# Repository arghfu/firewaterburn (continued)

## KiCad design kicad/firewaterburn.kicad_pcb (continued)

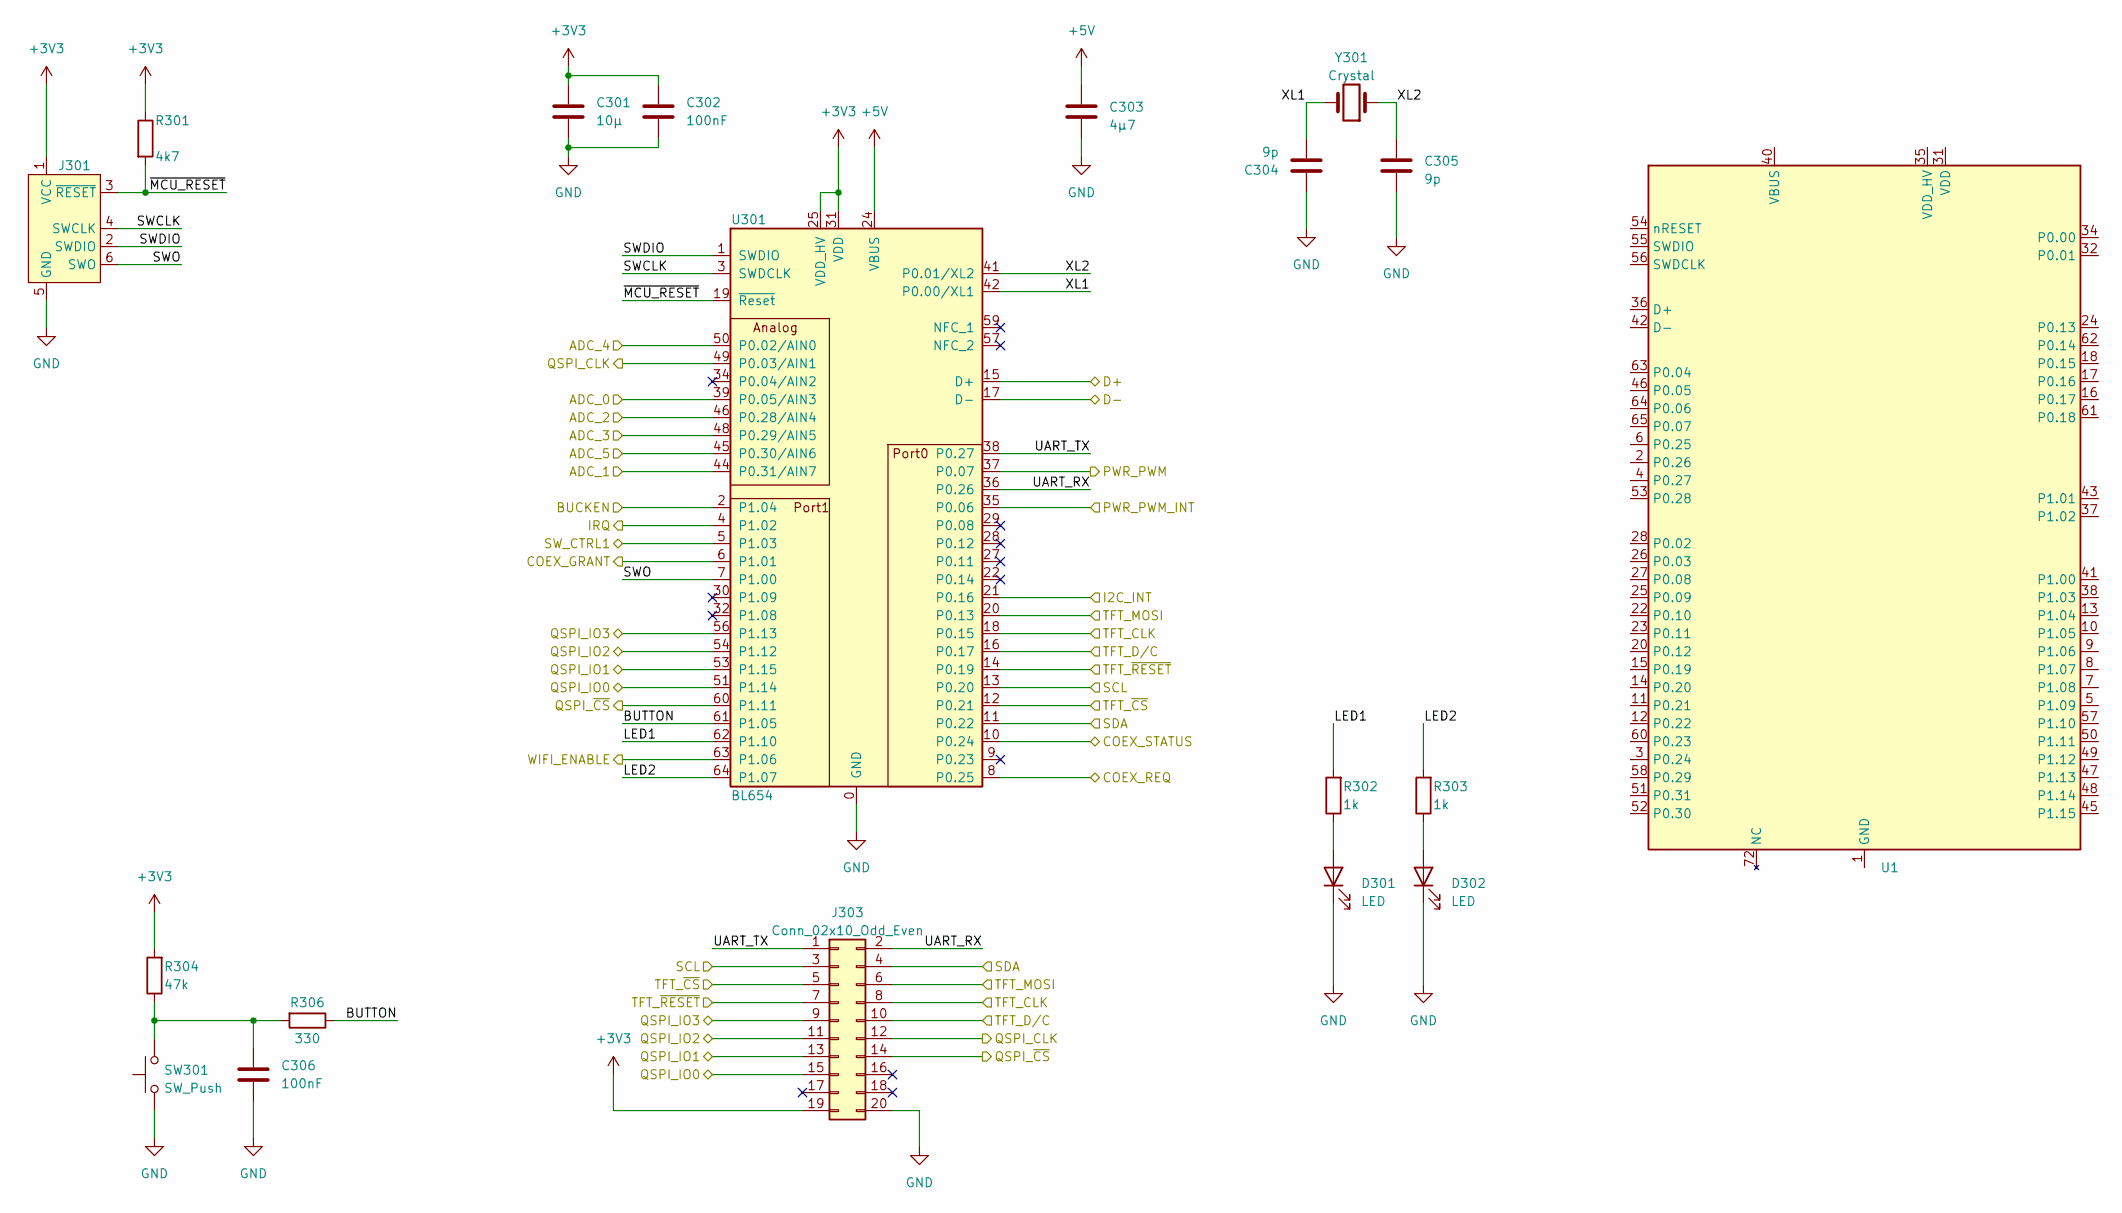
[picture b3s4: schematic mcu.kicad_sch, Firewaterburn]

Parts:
C301: 10µ; C_0603_1608Metric; Digikey 490-18214-1-ND
C302, C306: 100nF; C_0603_1608Metric; Digikey 1276-1006-1-ND
C303: 4µ7; C_0603_1608Metric; Digikey 478-06033D475KAT2ACT-ND
C304, C305: 9p; C_0603_1608Metric; Digikey 445-5627-1-ND
D301, D302: LED; LED_0603_1608Metric; Digikey 516-HSMS-C197CT-ND
J301: Conn_ARM_SWD_TagConnect_TC2030; Tag-Connect_TC2030-IDC-FP_2x03_P1.27mm_Vertical
J303: Conn_02x10_Odd_Even; PinHeader_2x10_P1.27mm_Vertical_SMD; Digikey 1175-1637-ND
R301: 4k7; R_0603_1608Metric; Digikey 311-4.70KHRCT-ND
R302, R303: 1k; R_0603_1608Metric; Digikey RNCP0603FTD1K00CT-ND
R304: 47k; R_0603_1608Metric
R306: 330; R_0603_1608Metric
SW301: SW_Push; SW_Push_SPST_NO_Alps_SKRK
U1: BL5340
U301: BL654; BL654-00001; Digikey 451-00001CT-ND
Y301: Crystal; CM8V-T1A-2Pin_2.0x1.2mm; Digikey 2195-CM8V-T1A-32.768KHZ-9PF-20PPM-TA-QC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

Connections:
+3V3: C301.1, C302.1, J301.1 (VCC), J303.19, R301.1, R304.2, U301.25 (VDD_HV), U301.31 (VDD); also elsewhere on the board
+5V: C303.1, U301.24 (VBUS); also elsewhere on the board
/D+: U301.15 (D+); also elsewhere on the board
/D-: U301.17 (D-); also elsewhere on the board
/analog/probe0: U301.39 (P0.05/AIN3); also elsewhere on the board
/analog/probe1: U301.44 (P0.31/AIN7); also elsewhere on the board
/analog/probe2: U301.46 (P0.28/AIN4); also elsewhere on the board
/analog/probe3: U301.48 (P0.29/AIN5); also elsewhere on the board
/analog/probe4: U301.50 (P0.02/AIN0); also elsewhere on the board
/analog/probe5: U301.45 (P0.30/AIN6); also elsewhere on the board
/fan_control/PWM: U301.37 (P0.07); also elsewhere on the board
/fan_control/TACHO: U301.35 (P0.06); also elsewhere on the board
/mcu/BUCKEN: U301.2 (P1.04); also elsewhere on the board
/mcu/BUTTON: R306.1, U301.61 (P1.05)
/mcu/COEX_GRANT: U301.6 (P1.01); also elsewhere on the board
/mcu/COEX_REQ: U301.8 (P0.25); also elsewhere on the board
/mcu/COEX_STATUS: U301.10 (P0.24); also elsewhere on the board
/mcu/I2C_INT: U301.21 (P0.16); also elsewhere on the board
/mcu/IRQ: U301.4 (P1.02); also elsewhere on the board
/mcu/LED1: R302.2, U301.62 (P1.10)
/mcu/LED2: R303.2, U301.64 (P1.07)
/mcu/QSPI_CLK: J303.12, U301.49 (P0.03/AIN1); also elsewhere on the board
/mcu/QSPI_IO0: J303.15, U301.51 (P1.14); also elsewhere on the board
/mcu/QSPI_IO1: J303.13, U301.53 (P1.15); also elsewhere on the board
/mcu/QSPI_IO2: J303.11, U301.54 (P1.12); also elsewhere on the board
/mcu/QSPI_IO3: J303.9, U301.56 (P1.13); also elsewhere on the board
/mcu/QSPI_~CS: J303.14, U301.60 (P1.11); also elsewhere on the board
/mcu/SCL: J303.3, U301.13 (P0.20); also elsewhere on the board
/mcu/SDA: J303.4, U301.11 (P0.22); also elsewhere on the board
/mcu/SWCLK: J301.4 (SWCLK), U301.3 (SWDCLK)
/mcu/SWDIO: J301.2 (SWDIO), U301.1 (SWDIO)
/mcu/SWO: J301.6 (SWO), U301.7 (P1.00)
/mcu/SW_CTRL1: U301.5 (P1.03); also elsewhere on the board
/mcu/TFT_CLK: J303.8, U301.18 (P0.15); also elsewhere on the board
/mcu/TFT_D/C: J303.10, U301.16 (P0.17); also elsewhere on the board
/mcu/TFT_MOSI: J303.6, U301.20 (P0.13); also elsewhere on the board
/mcu/TFT_~CS: J303.5, U301.12 (P0.21); also elsewhere on the board
/mcu/TFT_~RESET: J303.7, U301.14 (P0.19); also elsewhere on the board
/mcu/UART_RX: J303.2, U301.36 (P0.26)
/mcu/UART_TX: J303.1, U301.38 (P0.27)
/mcu/WIFI_ENABLE: U301.63 (P1.06); also elsewhere on the board
/mcu/XL1: C304.2, U301.42 (P0.00/XL1), Y301.2
/mcu/XL2: C305.1, U301.41 (P0.01/XL2), Y301.1
/mcu/~MCU_RESET: J301.3 (~RESET), R301.2, U301.19 (~Reset)
unnamed: C306.1, R304.1, R306.2, SW301.2
unnamed: D301.2 (A), R302.1
unnamed: D302.2 (A), R303.1

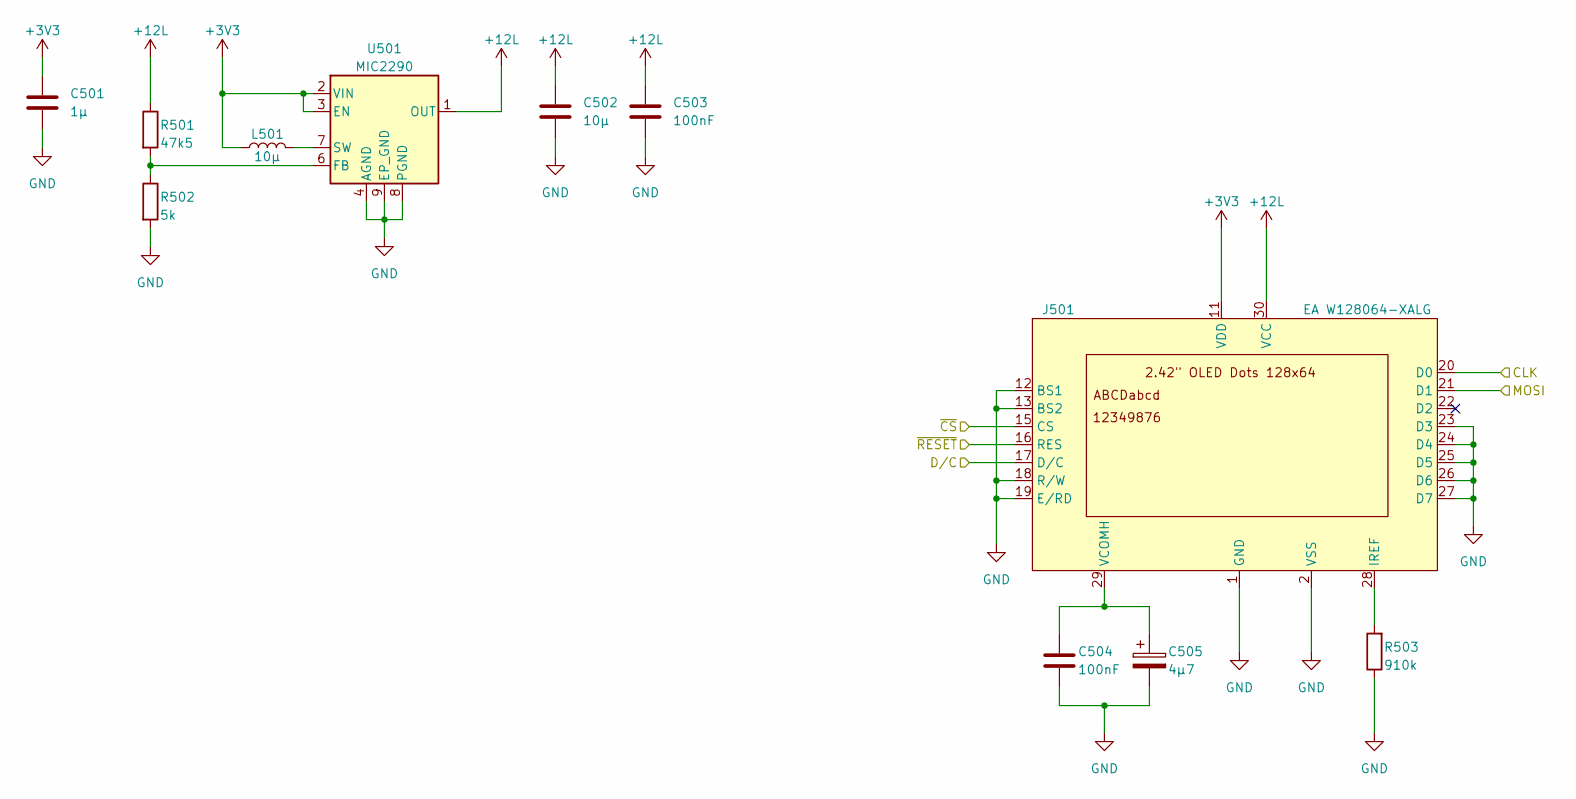
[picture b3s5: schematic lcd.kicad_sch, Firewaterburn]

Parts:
C501: 1µ; C_0402_1005Metric; Digikey 1276-1067-1-ND
C502: 10µ; C_0402_1005Metric; Digikey 490-GRM155R61A106ME11DCT-ND
C503: 100nF; C_0402_1005Metric; Digikey 478-7888-1-ND
C504: 100nF; C_0603_1608Metric; Digikey 1276-1006-1-ND
C505: 4µ7; CP_EIA-2012-15_AVX-P; Digikey 478-F981C475MMUAJ6CT-ND
J501: EA W128064-XALG; F32R-1A7H1-11031; Digikey EA W128064-XALG
L501: 10µ; L_Wuerth_MAPI-2510; Digikey 732-4851-1-ND
R501: 47k5; R_0402_1005Metric; Digikey 311-47.5KLRCT-ND
R502: 5k; R_0402_1005Metric; Digikey 13-RC0402FR-075KLCT-ND
R503: 910k; R_0603_1608Metric; Digikey 311-910KHRCT-ND
U501: MIC2290; Micrel_MLF-8-1EP_2x2mm_P0.5mm_EP0.8x1.3mm_ThermalVias; Digikey 576-1076-1-ND

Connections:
+3V3: C501.1, J501.11 (VDD), L501.1, U501.2 (VIN), U501.3 (EN); also elsewhere on the board
+12L: C502.1, C503.1, J501.30 (VCC), R501.1, U501.1 (OUT)
/mcu/TFT_CLK: J501.20 (D0); also elsewhere on the board
/mcu/TFT_D/C: J501.17 (D/C); also elsewhere on the board
/mcu/TFT_MOSI: J501.21 (D1); also elsewhere on the board
/mcu/TFT_~CS: J501.15 (CS); also elsewhere on the board
/mcu/TFT_~RESET: J501.16 (RES); also elsewhere on the board
unnamed: J501.28 (IREF), R503.2
unnamed: C504.1, C505.1, J501.29 (VCOMH)
unnamed: R501.2, R502.1, U501.6 (FB)
unnamed: L501.2, U501.7 (SW)

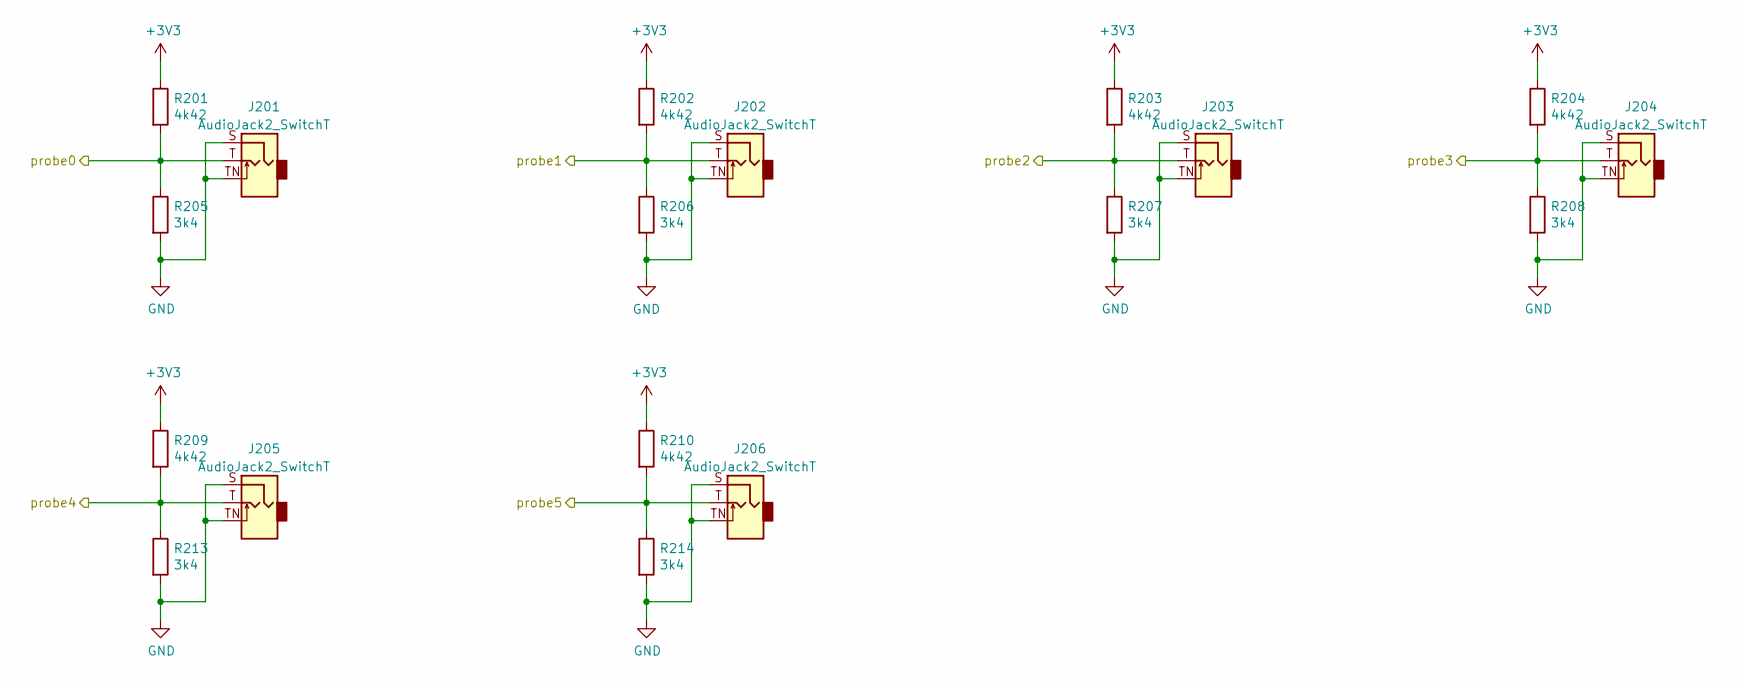
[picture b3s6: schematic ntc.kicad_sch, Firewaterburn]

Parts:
J201, J202, J203, J204, J205, J206: AudioJack2_SwitchT; MJ-2523; Digikey CP-2523MJCT-ND
R201, R202, R203, R204, R209, R210: 4k42; R_0603_1608Metric; Digikey RMCF0603FT4K42CT-ND
R205, R206, R207, R208, R213, R214: 3k4; R_0603_1608Metric; Digikey 311-3.40KHRCT-ND

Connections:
+3V3: R201.1, R202.1, R203.1, R204.1, R209.1, R210.1; also elsewhere on the board
/analog/probe0: J201.T, R201.2, R205.1; also elsewhere on the board
/analog/probe1: J202.T, R202.2, R206.1; also elsewhere on the board
/analog/probe2: J203.T, R203.2, R207.1; also elsewhere on the board
/analog/probe3: J204.T, R204.2, R208.1; also elsewhere on the board
/analog/probe4: J205.T, R209.2, R213.1; also elsewhere on the board
/analog/probe5: J206.T, R210.2, R214.1; also elsewhere on the board

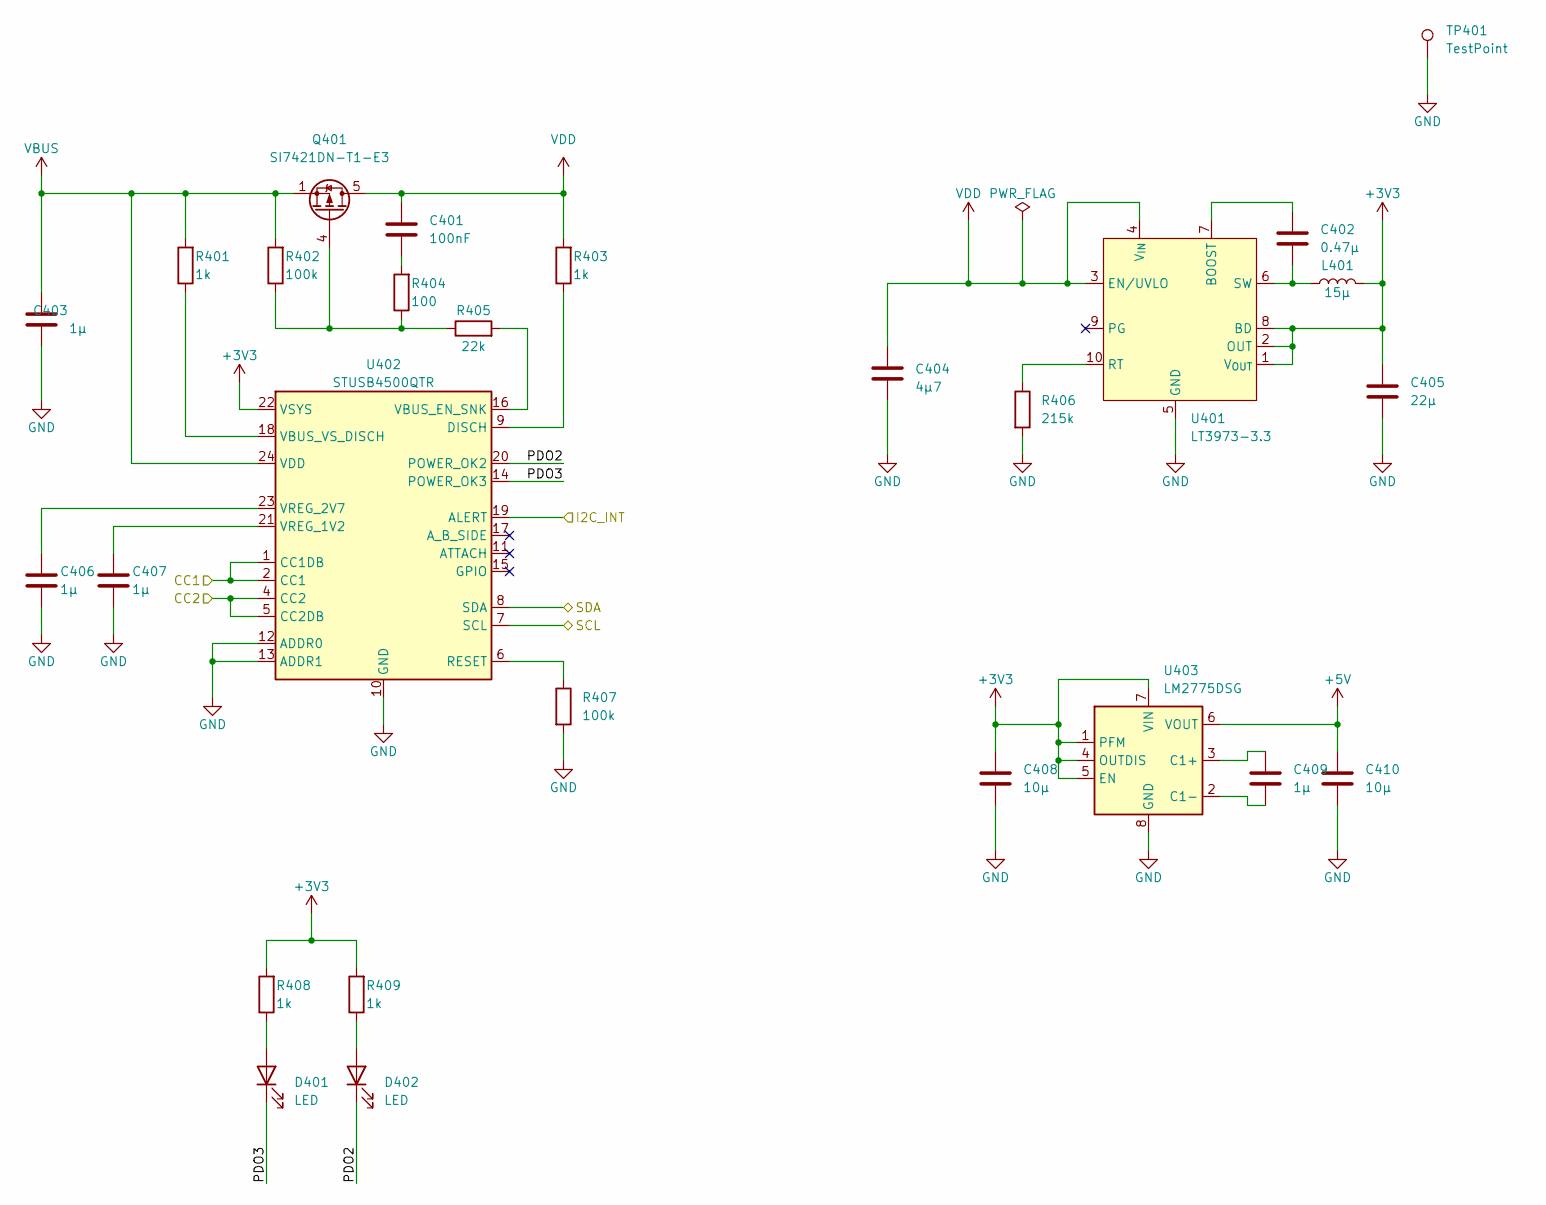
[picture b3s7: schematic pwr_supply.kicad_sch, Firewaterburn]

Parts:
C401: 100nF; C_0603_1608Metric; Digikey 1276-1006-1-ND
C402: 0.47µ; C_0603_1608Metric; Digikey 587-2670-1-ND
C403, C409: 1µ; C_0603_1608Metric; Digikey 1276-1102-1-ND
C404: 4µ7; C_0603_1608Metric; Digikey 478-06033D475KAT2ACT-ND
C405: 22µ; C_0603_1608Metric; Digikey 1276-7076-1-ND
C406, C407: 1µ; C_0402_1005Metric; Digikey 1276-1067-1-ND
C408, C410: 10µ; C_0603_1608Metric; Digikey 490-18214-1-ND
D401, D402: LED; LED_0603_1608Metric; Digikey 516-HSMS-C197CT-ND
L401: 15µ; L_TDK_VLS6045EX_VLS6045AF; Digikey 445-VLS3012HBX-150M-NCT-ND
Q401: SI7421DN-T1-E3; Vishay_PowerPAK_1212-8_Single; Digikey SI7421DN-T1-E3CT-ND
R401, R403: 1k; R_0603_1608Metric; Digikey RNCP0603FTD1K00
R402: 100k; R_0603_1608Metric; Digikey 311-100KHRCT-ND
R404: 100; R_0603_1608Metric; Digikey RNCP0603FTD100RCT-ND
R405: 22k; R_0603_1608Metric; Digikey 10-ERJ-H3EF2202VCT-ND
R406: 215k; R_0603_1608Metric; Digikey YAG5324CT-ND
R407: 100k; R_0402_1005Metric; Digikey 1292-WR04X1003FTLCT-ND
R408, R409: 1k; R_0603_1608Metric; Digikey RNCP0603FTD1K00CT-ND
TP401: TestPoint; TestPoint_Keystone_5015_Micro-Minature; Digikey 36-5015CT-ND
U401: LT3973-3.3; DFN-10-1EP_3x3mm_P0.5mm_EP1.65x2.38mm_ThermalVias; Digikey LT3973IDD-3.3#PBF-ND
U402: STUSB4500QTR; QFN-24-1EP_4x4mm_P0.5mm_EP2.7x2.7mm_ThermalVias; Digikey 497-18060-1-ND
U403: LM2775DSG; WSON-8-1EP_2x2mm_P0.5mm_EP0.9x1.6mm_ThermalVias; Digikey 296-42149-1-ND

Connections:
+3V3: C405.1, C408.1, L401.2, R408.2, R409.2, U401.1 (V_{OUT}), U401.2 (OUT), U401.8 (BD), U402.22 (VSYS), U403.1 (PFM), U403.4 (OUTDIS), U403.5 (EN), U403.7 (VIN); also elsewhere on the board
+5V: C410.1, U403.6 (VOUT); also elsewhere on the board
/mcu/I2C_INT: U402.19 (ALERT); also elsewhere on the board
/mcu/SCL: U402.7 (SCL); also elsewhere on the board
/mcu/SDA: U402.8 (SDA); also elsewhere on the board
/pwr_supply/CC1: U402.1 (CC1DB), U402.2 (CC1); also elsewhere on the board
/pwr_supply/CC2: U402.4 (CC2), U402.5 (CC2DB); also elsewhere on the board
/pwr_supply/PDO2: D402.1 (K), U402.20 (POWER_OK2)
/pwr_supply/PDO3: D401.1 (K), U402.14 (POWER_OK3)
unnamed: C401.2, R404.2
unnamed: D401.2 (A), R408.1
unnamed: D402.2 (A), R409.1
unnamed: Q401.4 (G), R402.1, R404.1, R405.1
unnamed: C402.1, U401.7 (BOOST)
unnamed: R406.1, U401.10 (RT)
unnamed: C402.2, L401.1, U401.6 (SW)
unnamed: R403.1, U402.9 (DISCH)
unnamed: R407.1, U402.6 (RESET)
unnamed: R405.2, U402.16 (VBUS_EN_SNK)
unnamed: R401.1, U402.18 (VBUS_VS_DISCH)
unnamed: C407.1, U402.21 (VREG_1V2)
unnamed: C406.1, U402.23 (VREG_2V7)
unnamed: C409.2, U403.3 (C1+)
unnamed: C409.1, U403.2 (C1-)
VBUS: C403.1, Q401.1 (S), Q401.2 (S), Q401.3 (S), R401.2, R402.2, U402.24 (VDD); also elsewhere on the board
VDD: C401.1, C404.1, Q401.5 (D), R403.2, U401.3 (EN/UVLO), U401.4 (V_{IN}); also elsewhere on the board

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
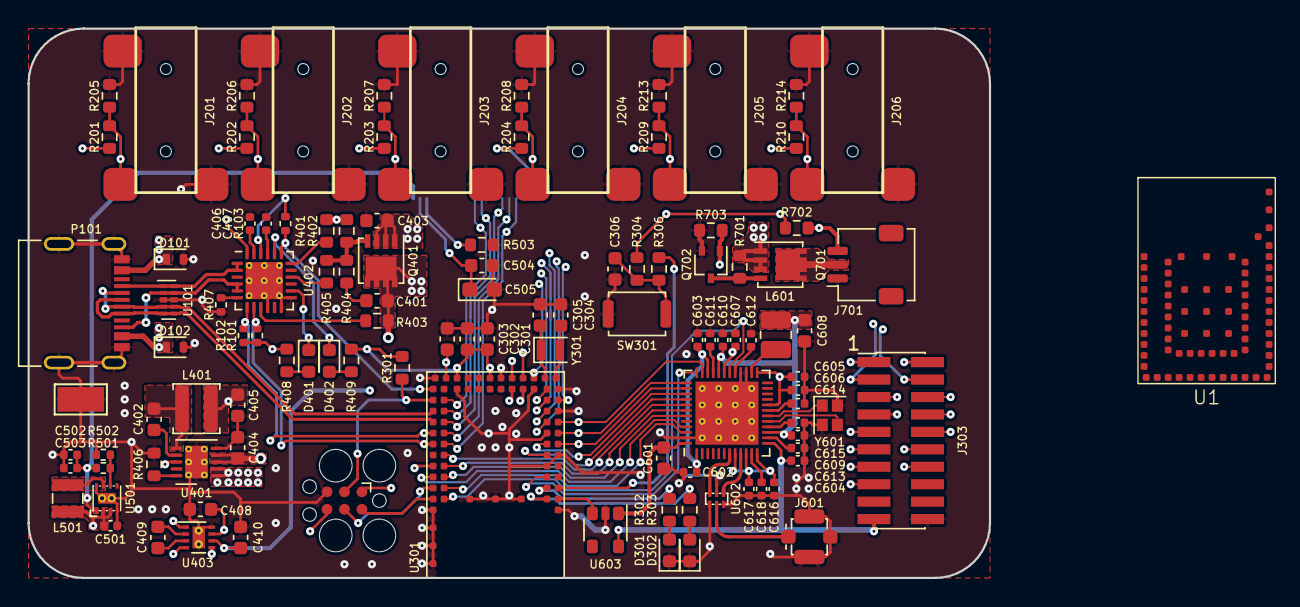
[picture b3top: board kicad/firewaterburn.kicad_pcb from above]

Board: 4 copper layers, 70.0 x 40.0 mm, 112 parts (1 on the bottom side), 92 nets.

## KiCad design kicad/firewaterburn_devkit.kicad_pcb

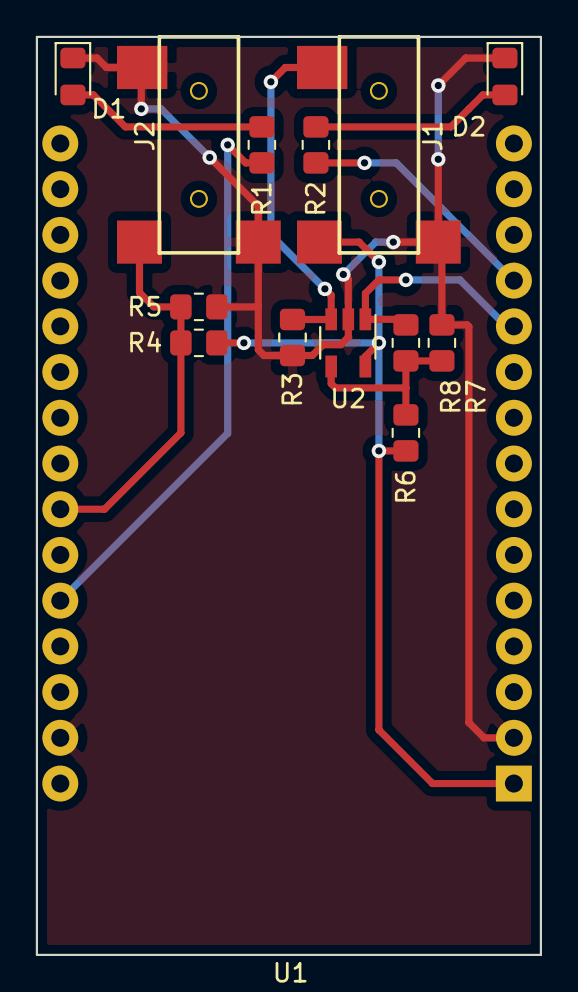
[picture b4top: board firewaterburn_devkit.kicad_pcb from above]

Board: 2 copper layers, 28.0 x 51.0 mm, 14 parts (0 on the bottom side), 10 nets.

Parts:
D1, D2: LED; LED_0805_2012Metric_Pad1.15x1.40mm_HandSolder
J1, J2: AudioJack2_SwitchT; MJ-2523
R1, R2: 130; R_0805_2012Metric_Pad1.20x1.40mm_HandSolder
R3, R5, R7: 2k49; R_0805_2012Metric_Pad1.20x1.40mm_HandSolder
R4: 3k24; R_0805_2012Metric_Pad1.20x1.40mm_HandSolder
R6: 4k02; R_0805_2012Metric_Pad1.20x1.40mm_HandSolder
R8: 2k26; R_0805_2012Metric_Pad1.20x1.40mm_HandSolder
U1: ESP-WROOM-32; esp-wroom-32-devkit
U2: LT6202; TSOT-23-5

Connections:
+3V3: J1.T, R4.2, R6.2, U1.1, U2.5
/T_lin: J2.T, R4.1, R5.1, U1.22
/T_op: R8.2, U1.11, U2.1
GND: D1.1, D2.1, J1.TN, J2.S, J2.TN, R3.1, R5.2, R7.1, U1.2, U1.17, U2.2
unnamed: D1.2, R1.1
unnamed: D2.2, R2.1
unnamed: J1.S, R3.2, U2.3
unnamed: R1.2, U1.20
unnamed: R2.2, U1.12
unnamed: R6.1, R7.2, R8.1, U2.4

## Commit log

2021-08-22 add basic hardware to schematic
2021-09-03 save preliminary work
2022-01-08 add all parts to schematic
2022-01-24 refactor KiCAD Project to v6
2022-01-25 add rules to .gitignore
2022-01-25 add connection to lcd
    import parts into pcbnew
2022-02-26 route complete pcb
2022-03-14 add FreeCAD model for enclosure
2023-02-19 rework pcb
2023-02-26 add all digikeys numbers to schematic
2023-04-01 add nrf52840 board
2023-04-01 add initial zephyr project
2023-04-01 refactor project structure
2023-05-01 rework board
    add nrf 7002
    add oled display
2023-07-22 new board
2024-01-28 upgrade 2 KiCAD 8.0
2024-05-20 update pcb
2024-05-20 fix fire_board.dts for wlan0 nrf7002
